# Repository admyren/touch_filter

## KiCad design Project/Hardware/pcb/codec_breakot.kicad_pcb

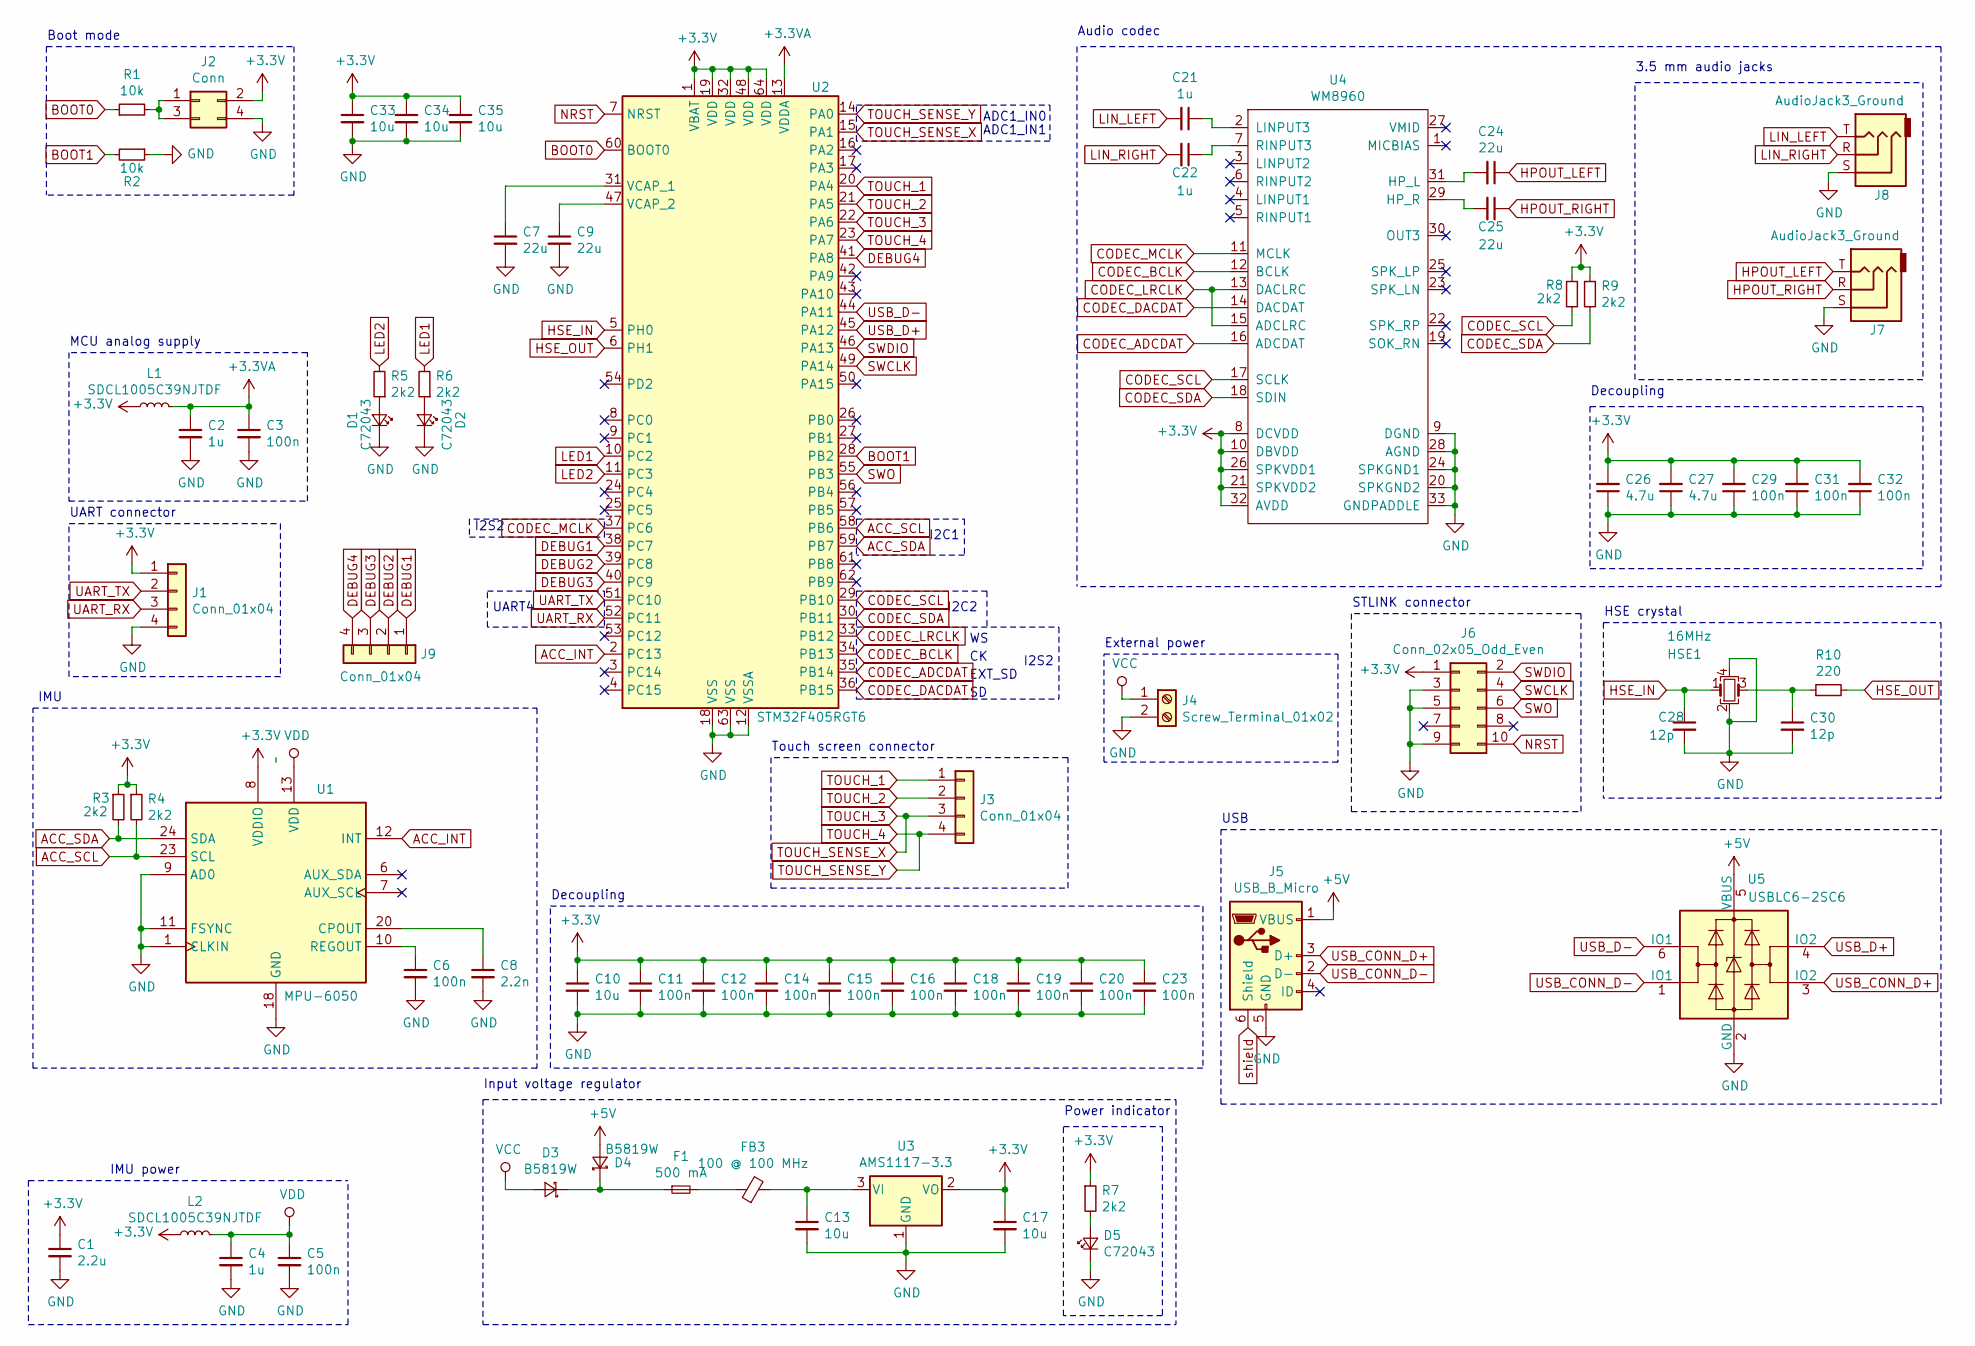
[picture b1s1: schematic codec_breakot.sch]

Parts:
C1: 2.2u; C_0603; LCSC Part # C23630
C2, C4, C21, C22: 1u; C_0603; LCSC Part # C15849
C3, C5, C6, C11, C12, C14, C15, C16, C18, C19, C20, C23, C29, C31, C32: 100n; C_0603; LCSC Part # C14663
C7, C9, C24, C25: 22u; C_0805; LCSC Part # C45783
C8: 2.2n; C_0402; LCSC Part # C1531
C10, C13, C17, C33, C34, C35: 10u; C_0805; LCSC Part # C15850
C26, C27: 4.7u; C_0603; LCSC Part # C19666
C28, C30: 12p; C_0402; LCSC Part # C1547
D1, D2, D5: C72043; LED_0603; LCSC Part # C72043
D3, D4: B5819W; D_SOD-123; LCSC Part # C8598
F1: 500 mA; Fuse_SMD1206_HandSoldering
FB3: 100 @ 100 MHz; L_0805_2012Metric
HSE1: 16MHz; Crystal_SMD_3225-4pin_3.2x2.5mm; LCSC Part # C13738
J1: Conn_01x04; Pin_Header_Straight_1x04_Pitch2.54mm
J2: Conn; Pin_Header_Straight_2x02_Pitch2.54mm
J3: Conn_01x04; conn_pad_SMD_1x4_1mm
J4: Screw_Terminal_01x02; Pin_Header_Straight_1x02_Pitch2.54mm
J5: USB_B_Micro; USB_micro_smd
J6: Conn_02x05_Odd_Even; Pin_Header_Straight_2x05_Pitch2.54mm
J7, J8: AudioJack3_Ground; Jack_3.5mm_CUI_SJ-3523-SMT_Horizontal
J9: Conn_01x04; Pin_Header_Straight_1x04_Pitch1.27mm
L1, L2: SDCL1005C39NJTDF; L_0402_1005Metric; LCSC Part # C26443
R1, R2: 10k; R_0402; LCSC Part # C25744
R3, R4, R5, R6, R7, R8, R9: 2k2; R_0402; LCSC Part # C25879
R10: 220; R_0603; LCSC Part # C22962
U1: MPU-6050; QFN-24_4x4_Pitch0.5mm; LCSC Part # C24112
U2: STM32F405RGT6; LQFP-64_10x10mm_Pitch0.5mm; LCSC Part # C15742
U3: AMS1117-3.3; SOT-223-3_TabPin2; LCSC Part # C6186
U4: WM8960; QFN-32-1EP_5x5mm_Pitch0.5mm; LCSC Part # C18752
U5: USBLC6-2SC6; SOT-23-6; LCSC Part # C7519

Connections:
+3.3VA: C2.1, C3.1, L1.2, U2.13 (VDDA)
+3V3: C1.1, C10.1, C11.1, C12.1, C14.1, C15.1, C16.1, C17.1, C18.1, C19.1, C20.1, C23.1, C26.2, C27.2, C29.2, C31.2, C32.2, C33.1, C34.1, C35.1, J1.1, J2.2, J6.1, L1.1, L2.1, R3.1, R4.1, R7.1, R8.1, R9.1, U1.8 (VDDIO), U2.1 (VBAT), U2.19 (VDD), U2.32 (VDD), U2.48 (VDD), U2.64 (VDD), U3.2 (VO), U4.8 (DCVDD), U4.10 (DBVDD), U4.21 (SPKVDD2), U4.26 (SPKVDD1), U4.32 (AVDD)
+5V: D4.2 (A), J5.1 (VBUS), U5.5 (VBUS)
ACC_INT: U1.12 (INT), U2.2 (PC13)
ACC_SCL: R4.2, U1.23 (SCL), U2.58 (PB6)
ACC_SDA: R3.2, U1.24 (SDA), U2.59 (PB7)
BOOT0: R1.1, U2.60 (BOOT0)
BOOT1: R2.2, U2.28 (PB2)
CODEC_ADCDAT: U2.35 (PB14), U4.16 (ADCDAT)
CODEC_BCLK: U2.34 (PB13), U4.12 (BCLK)
CODEC_DACDAT: U2.36 (PB15), U4.14 (DACDAT)
CODEC_LRCLK: U2.33 (PB12), U4.13 (DACLRC), U4.15 (ADCLRC)
CODEC_MCLK: U2.37 (PC6), U4.11 (MCLK)
CODEC_SCL: R8.2, U2.29 (PB10), U4.17 (SCLK)
CODEC_SDA: R9.2, U2.30 (PB11), U4.18 (SDIN)
DEBUG1: J9.1, U2.38 (PC7)
DEBUG2: J9.2, U2.39 (PC8)
DEBUG3: J9.3, U2.40 (PC9)
DEBUG4: J9.4, U2.41 (PA8)
GND: C1.2, C2.2, C3.2, C4.2, C5.2, C6.2, C7.2, C8.2, C9.2, C10.2, C11.2, C12.2, C13.2, C14.2, C15.2, C16.2, C17.2, C18.2, C19.2, C20.2, C23.2, C26.1, C27.1, C28.2, C29.1, C30.2, C31.1, C32.1, C33.2, C34.2, C35.2, D1.1 (K), D2.1 (K), D5.1 (K), HSE1.2, HSE1.4, J1.4, J2.4, J4.2, J5.5 (GND), J6.3, J6.5, J6.9, J7.S, J8.S, R2.1, U1.1 (CLKIN), U1.9 (AD0), U1.11 (FSYNC), U1.18 (GND), U2.12 (VSSA), U2.18 (VSS), U2.63 (VSS), U3.1 (GND), U4.9 (DGND), U4.20 (SPKGND2), U4.24 (SPKGND1), U4.28 (AGND), U4.33 (GNDPADDLE), U5.2 (GND)
HPOUT_LEFT: C24.1, J7.T
HPOUT_RIGHT: C25.1, J7.R
HSE_IN: C28.1, HSE1.1, U2.5 (PH0)
HSE_OUT: R10.2, U2.6 (PH1)
LED1: R6.2, U2.10 (PC2)
LED2: R5.2, U2.11 (PC3)
LIN_LEFT: C21.2, J8.T
LIN_RIGHT: C22.2, J8.R
NRST: J6.10, U2.7 (NRST)
unnamed: C6.1, U1.10 (REGOUT)
unnamed: C7.1, U2.31 (VCAP_1)
unnamed: C8.1, U1.20 (CPOUT)
unnamed: C9.1, U2.47 (VCAP_2)
unnamed: C13.1, FB3.2, U3.3 (VI)
unnamed: C21.1, U4.2 (LINPUT3)
unnamed: C22.1, U4.7 (RINPUT3)
unnamed: C24.2, U4.31 (HP_L)
unnamed: C25.2, U4.29 (HP_R)
unnamed: C30.1, HSE1.3, R10.1
unnamed: D1.2 (A), R5.1
unnamed: D2.2 (A), R6.1
unnamed: D3.1 (K), D4.1 (K), F1.1
unnamed: D5.2 (A), R7.2
unnamed: F1.2, FB3.1
unnamed: J2.1, J2.3, R1.2
SWCLK: J6.4, U2.49 (PA14)
SWDIO: J6.2, U2.46 (PA13)
SWO: J6.6, U2.55 (PB3)
TOUCH_1: J3.1, U2.20 (PA4)
TOUCH_2: J3.2, U2.21 (PA5)
TOUCH_3: J3.3, U2.15 (PA1), U2.22 (PA6)
TOUCH_4: J3.4, U2.14 (PA0), U2.23 (PA7)
UART_RX: J1.3, U2.52 (PC11)
UART_TX: J1.2, U2.51 (PC10)
USB_CONN_D+: J5.3 (D+), U5.3 (IO2)
USB_CONN_D-: J5.2 (D-), U5.1 (IO1)
USB_D+: U2.45 (PA12), U5.4 (IO2)
USB_D-: U2.44 (PA11), U5.6 (IO1)
VCC: D3.2 (A), J4.1
VDD: C4.1, C5.1, L2.2, U1.13 (VDD)
shield: J5.6 (Shield)

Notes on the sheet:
Input voltage regulator
Power indicator
Decoupling
3.5 mm audio jacks
Audio codec
USB
STLINK connector
HSE crystal
Boot mode
MCU analog supply
IMU power
I2C2
I2S2
I2C1
UART4
ADC1_IN0
ADC1_IN1
IMU
Touch screen connector
UART connector
External power
EXT_SD

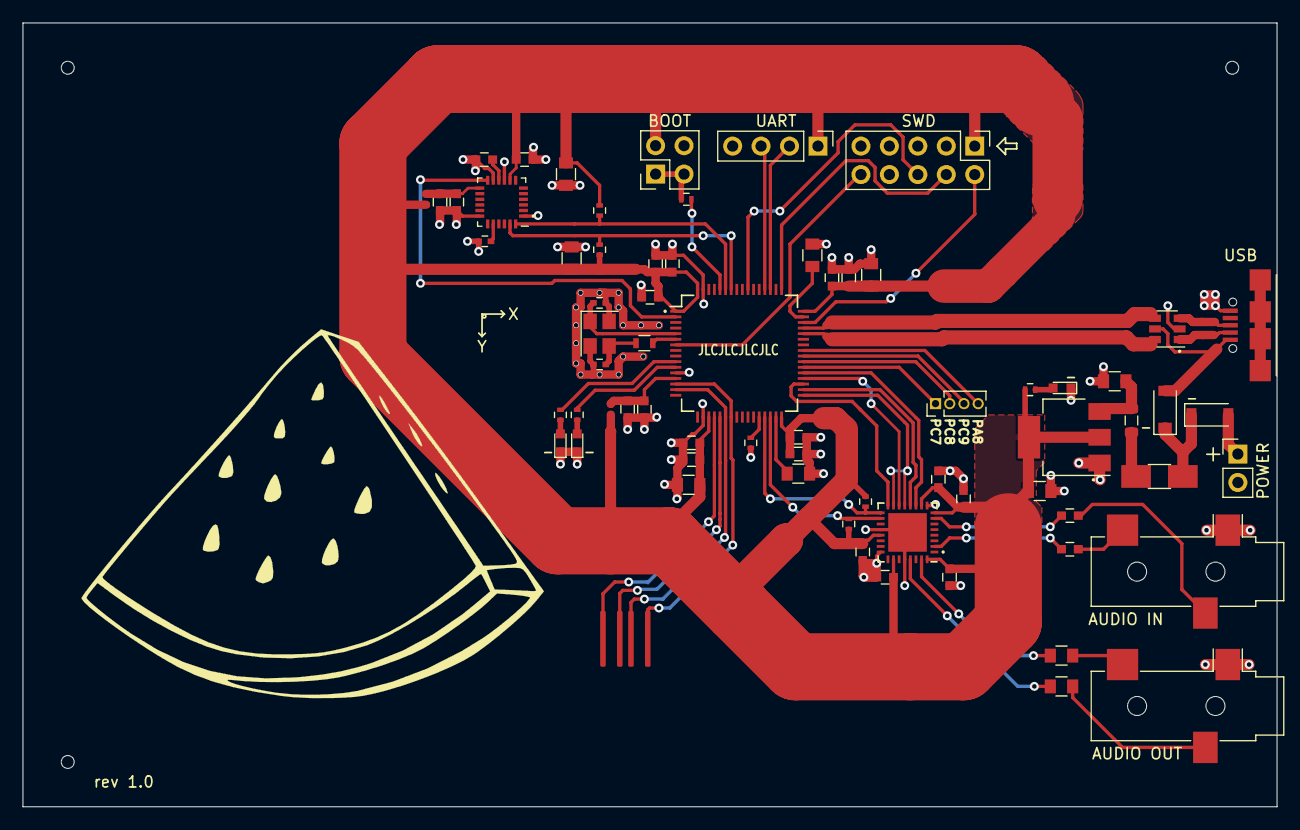
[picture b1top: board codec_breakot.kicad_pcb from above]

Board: 2 copper layers, 112.0 x 70.0 mm, 72 parts (0 on the bottom side), 60 nets.

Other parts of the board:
TOOLING HOLE: jlcpcb_tooling_hole
TOOLING HOLE#2, TOOLING HOLE#3: jlcpcb_tooling_hole

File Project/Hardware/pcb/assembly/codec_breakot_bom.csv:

Comment,Designator,Footprint,LCSC
"2.2u","C1","Capacitors_SMD:C_0603","C23630"
"10u","C10,C13,C17,C33,C34,C35","Capacitors_SMD:C_0805","C15850"
"1u","C2,C4,C21,C22","Capacitors_SMD:C_0603","C15849"
"22u","C7,C9,C24,C25","Capacitors_SMD:C_0805","C45783"
"4.7u","C26,C27","Capacitors_SMD:C_0603","C19666"
"12p","C28,C30","Capacitors_SMD:C_0402","C1547"
"100n","C3,C5,C6,C11,C12,C14,C15,C16,C18,C19,C20,C23,C29,C31,C32","Capacitors_SMD:C_0603","C14663"
"2.2n","C8","Capacitors_SMD:C_0402","C1531"
"B5819W","D3,D4","Diodes_SMD:D_SOD-123","C8598"
"C72043","D1,D2,D5","LEDs:LED_0603","C72043"
"500 mA","F1","Fuse_Holders_and_Fuses:Fuse_SMD1206_HandSoldering",""
"100 @ 100 MHz","FB3","Inductor_SMD:L_0805_2012Metric",""
"16MHz","HSE1","Crystals:Crystal_SMD_3225-4pin_3.2x2.5mm","C13738"
"Conn_01x04","J1","Pin_Headers:Pin_Header_Straight_1x04_Pitch2.54mm",""
"Conn","J2","Pin_Headers:Pin_Header_Straight_2x02_Pitch2.54mm",""
"Conn_01x04","J3","egna_footprints:conn_pad_SMD_1x4_1mm",""
"Screw_Terminal_01x02","J4","Pin_Headers:Pin_Header_Straight_1x02_Pitch2.54mm",""
"USB_B_Micro","J5","egna_footprints:USB_micro_smd",""
"Conn_02x05_Odd_Even","J6","Pin_Headers:Pin_Header_Straight_2x05_Pitch2.54mm",""
"AudioJack3_Ground","J7,J8","Connector_Audio:Jack_3.5mm_CUI_SJ-3523-SMT_Horizontal",""
"Conn_01x04","J9","Pin_Headers:Pin_Header_Straight_1x04_Pitch1.27mm",""
"SDCL1005C39NJTDF","L1,L2","Inductor_SMD:L_0402_1005Metric","C26443"
"10k","R1,R2","Resistors_SMD:R_0402","C25744"
"220","R10","Resistors_SMD:R_0603","C22962"
"2k2","R3,R4,R5,R6,R7,R8,R9","Resistors_SMD:R_0402","C25879"
"MPU-6050","U1","egna_footprints:QFN-24_4x4_Pitch0.5mm","C24112"
"STM32F405RGT6","U2","Housings_QFP:LQFP-64_10x10mm_Pitch0.5mm","C15742"
"AMS1117-3.3","U3","TO_SOT_Packages_SMD:SOT-223-3_TabPin2","C6186"
"WM8960","U4","Housings_DFN_QFN:QFN-32-1EP_5x5mm_Pitch0.5mm","C18752"
"USBLC6-2SC6","U5","TO_SOT_Packages_SMD:SOT-23-6","C7519"

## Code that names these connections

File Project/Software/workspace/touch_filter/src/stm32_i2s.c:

/*
 * stm32_i2s.c
 *
 *  Created on: 11 sep. 2021
 *      Author: Myren
 */
#include <stdint.h>

#include "stm32f405xx.h"
#include "stm32_i2s.h"
#include "stm32_dma.h"

void (*I2S_tx_ready_callb)(void) = 0;
void (*I2S_rx_ready_callb)(void) = 0;


void i2s_config(uint16_t* rx_buff, uint16_t* tx_buff, uint32_t buff_size)
{
   /* Struct for configuring DMA */
   DMA_InitVals DMA_init;

   /* I2S2ext, I2S2 (SPI2) */

   /* Enable I2S2 (SPI2) peripheral clock */
   RCC->APB1ENR |= (1 << 14);

   /* Configure GPIO used by I2S */
   /*
   MCLK - PC6
   LRCLK (WS) - PB12
   BCLK (CK) - PB13
   ADCDAT (EXT_SD) - PB14
   DACDAT (SD) - PB15
   */

   /* Enable GPIOB peripheral clock */
   RCC->AHB1ENR |= (1 << 1);
   /* Enable GPIOC peripheral clock */
   RCC->AHB1ENR |= (1 << 2);
   /* Alternate function */
   GPIOB->MODER |= (2 << 30) | (2 << 28) | (2 << 26) | (2 << 24);
   GPIOC->MODER |= (2 << 12);
   /* I2S2ext is on AF6, I2S2 is on AF5 */
   GPIOB->AFR[1] |= (5 << 28) | (6 << 24) | (5 << 20) | (5 << 16);
   GPIOC->AFR[0] |= (5 << 24);

   /* Set ODD bit and I2SDIV value */
   SPI2->I2SPR |= (1 << 8) | 3u;

   /* Select clock polarity */
   SPI2->I2SCFGR &= ~(1 << 3);

   /* Enable master output clock to audio CODEC */
   SPI2->I2SPR |= (1 << 9);

   /* Select mode: I2S */
   SPI2->I2SCFGR |= (1 << 11);

   /* Chose I2S standard */
   SPI2->I2SCFGR &= ~(3u << 4);

   /* Select data length, 16-bit */
   SPI2->I2SCFGR &= ~(3u << 1);

   /* Select nr of bits per channel, 16-bit */
   SPI2->I2SCFGR &= ~(0x1);

   /* Select I2S master transmit mode */
   SPI2->I2SCFGR |= (2u << 8);

   /***** Enable I2S2ext in slave receiver mode to achieve full duplex com *****/
   /* Select mode: I2S */
   I2S2ext->I2SCFGR |= (1 << 11);
   /* Chose I2S standard */
   I2S2ext->I2SCFGR &= ~(3u << 4);
   /* Select data length, 16-bit */
   I2S2ext->I2SCFGR &= ~(3u << 1);
   /* Select nr of bits per channel, 16-bit */
   I2S2ext->I2SCFGR &= ~(0x1);
   /* Select I2S slave receiver mode */
   I2S2ext->I2SCFGR |= (1u << 8);

#if 1
   /* Configure DMA */
   /* DMA clocks */
   RCC->AHB1ENR |= (1 << 22) | (1 << 21);
   /* I2S2 TX uses stream 4, ch 0. I2Sext RX uses stream 2, ch 2  */
   /* Enable TX DMA  */
   SPI2->CR2 |= (1 << 1);
   /* Enable RX DMA */
   I2S2ext->CR2 |= (1 << 0);


   DMA_init.channel = 0;             /* DMA channel */
   DMA_init.periphDataSize = SIZE_HALF_WORD;      /* Peripheral data size */
   DMA_init.memDataSize = SIZE_HALF_WORD;         /* Memory data size */
   DMA_init.direction = 1;           /* Direction, memory->peripheral(1) or peripheral->memory(0) */
   DMA_init.bufferSize = buff_size;          /* Number of element in the DMA buffer */
   DMA_init.periphAddr = (uint32_t)(&SPI2->DR);          /* Address to peripheral data register */
   DMA_init.memAddr = (uint32_t)tx_buff;             /* Address to first element of DMA buffer */
   DMA_init.halfIntEnable = 0;       /* DMA half transfer complete interrupt enable */
   DMA_init.compIntEnable = 1;       /* DMA transfer complete interrupt enable */
   DMA_init.mode = 1;                /* Circular mode or not */
   DMA_init.dma_enable = 1;          /* DMA enable */

   /* Enable DMA for I2S2 TX */
   DMA_config(DMA1_Stream4, DMA_init);

   DMA_init.channel = 2;             /* DMA channel */
   DMA_init.periphDataSize = SIZE_HALF_WORD;      /* Peripheral data size */
   DMA_init.memDataSize = SIZE_HALF_WORD;         /* Memory data size */
   DMA_init.direction = 0;           /* Direction, memory->peripheral(1) or peripheral->memory(0) */
   DMA_init.bufferSize = buff_size;          /* Number of element in the DMA buffer */
   DMA_init.periphAddr = (uint32_t)(&I2S2ext->DR);          /* Address to peripheral data register */
   DMA_init.memAddr = (uint32_t)rx_buff;             /* Address to first element of DMA buffer */
   DMA_init.halfIntEnable = 0;       /* DMA half transfer complete interrupt enable */
   DMA_init.compIntEnable = 1;       /* DMA transfer complete interrupt enable */
   DMA_init.mode = 1;                /* Circular mode or not */
   DMA_init.dma_enable = 1;          /* DMA enable */

   /* Enable DMA for I2S2ext RX */
   DMA_config(DMA1_Stream2, DMA_init);

   NVIC_SetPriorityGrouping(2);
   NVIC_SetPriority (DMA1_Stream2_IRQn, 8);
   NVIC_EnableIRQ(DMA1_Stream2_IRQn);

   NVIC_SetPriorityGrouping(2);
   NVIC_SetPriority (DMA1_Stream4_IRQn, 8);
   NVIC_EnableIRQ(DMA1_Stream4_IRQn);
#endif

   /* Enable I2S */
   SPI2->I2SCFGR |= (1 << 10);
   I2S2ext->I2SCFGR |= (1 << 10);

}

void I2S_register_rx_complete_callback(void (*func)(void))
{
   I2S_rx_ready_callb = func;
}

void I2S_register_tx_complete_callback(void (*func)(void))
{
   I2S_tx_ready_callb = func;
}


void DMA1_Stream2_IRQHandler(void)
{
   // Transfer complete interrupt?
   if(DMA1->LISR & (1 << 21))
   {
      // Clear interrupt flag
      DMA1->LIFCR |= 1 << 21;

      if (I2S_rx_ready_callb != 0)
      {
         I2S_rx_ready_callb();
      }
   }
}

void DMA1_Stream4_IRQHandler(void)
{
   // Transfer complete interrupt?
   if(DMA1->HISR & (1 << 5))
   {
      // Clear interrupt flag
      DMA1->HIFCR |= 1 << 5;

      if(I2S_tx_ready_callb != 0)
      {
         I2S_tx_ready_callb();
      }
   }
}

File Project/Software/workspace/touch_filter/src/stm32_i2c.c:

/*
 * stm32_i2c.c
 *
 *  Created on: 28 aug. 2021
 *      Author: Myren
 */

/*
 * i2c_drv.c
 *
 *  Created on: 11 jan. 2020
 *      Author: Myren
 */

#include "stm32f405xx.h"
#include "stm32_i2c.h"
#include "stm32_gpio.h"
#include "stm32_peripherals.h"

/*
 Codec uses I2C2, SCL: PB10 SDA: PB11
 IMU uses I2C1, SCL: PB6 SDA: PB7
*/

void i2c1_init(I2C_TypeDef* hi2c)
{
   // This initializes the I2C1 peripheral
   // and its corresponding GPIOs

   uint32_t pclk1;
   const uint32_t scl_freq = 100000;
   gpio_config_t gpio_conf;


   gpio_conf.mode = gpio_af;
   gpio_conf.output_type = gpio_ood;
   gpio_conf.output_speed = gpio_hs;
   gpio_conf.pull_up_down = gpio_no_pull;
   gpio_conf.alternate_func = gpio_af_4;
   gpio_conf.lock = gpio_lock_off;
   gpio_conf.pins = gpio_pin_10 | gpio_pin_11;

   // Enable GPIOB peripheral clock
   RCC->AHB1ENR |= (1 << 1);

   //gpio_init(GPIOB, &gpio_conf);

#if 1
   // Alternate function
   GPIOB->MODER |= (2 << 14) | (2 << 12);
   // AF4 alternate function
   GPIOB->AFR[0] |= (4 << 28) | (4 << 24);
#endif

   // Enable I2C1 peripheral clock
   RCC->APB1ENR |= (1 << 21);

   // Periperal clock freqiency in MHz, 50MHz >= FREQ >= 2MHz
   hi2c->CR2 |= (0x001f & 42u);

   // Set fast mode (400khz)
   //I2C1->CCR |= (1 << 15);

   // Set fast mode duty
   // I2C1->CCR |= (1 << 14);
   // Get frequency of peripheral clock
   //pclk1 = HAL_RCC_GetPCLK1Freq();
   pclk1 = 42000000;
   // Clock control, for an SCL freq. of approx. 100 kHz
   //hi2c->CCR |= 0x0fff & (2*pclk1/scl_freq);
   /* 100 kHz */
   hi2c->CCR |= 210;

   // Maximum rise time of SCL, programmed with
   // rise =(max_rise_t/T_PCLK1)+1. Where T_PCLK1 is the
   // period time of the peripheral clock and max_rise_t
   // is the maximum rise time of SCL specified by the I2C specification.

   //hi2c->TRISE |= (0x003f & ((pclk1/1000) + 1));
   hi2c->TRISE |= (0x003f & ((pclk1/1000000) + 1));

   // Peripheral enable
   hi2c->CR1 |= (1 << 0);
}

void i2c2_init(I2C_TypeDef* hi2c)
{
   // This initializes the I2C2 peripheral
   // and its corresponding GPIOs

   uint32_t pclk1;
   const uint32_t scl_freq = 100000;
   gpio_config_t gpio_conf;


   gpio_conf.mode = gpio_af;
   gpio_conf.output_type = gpio_ood;
   gpio_conf.output_speed = gpio_hs;
   gpio_conf.pull_up_down = gpio_no_pull;
   gpio_conf.alternate_func = gpio_af_4;
   gpio_conf.lock = gpio_lock_off;
   gpio_conf.pins = gpio_pin_10 | gpio_pin_11;

   // Enable GPIOB peripheral clock
   RCC->AHB1ENR |= (1 << 1);

   //gpio_init(GPIOB, &gpio_conf);

#if 1
   // Alternate function
   GPIOB->MODER |= (2 << 22) | (2 << 20);
   // AF4 alternate function
   GPIOB->AFR[1] |= (4 << 12) | (4 << 8);
#endif

   // Enable I2C2 peripheral clock
   RCC->APB1ENR |= (1 << 22);

   // Periperal clock freqiency in MHz, 50MHz >= FREQ >= 2MHz
   hi2c->CR2 |= (0x001f & 42u);

   // Set fast mode (400khz)
   //I2C1->CCR |= (1 << 15);

   // Set fast mode duty
   // I2C1->CCR |= (1 << 14);
   // Get frequency of peripheral clock
   //pclk1 = HAL_RCC_GetPCLK1Freq();
   pclk1 = 42000000;
   // Clock control, for an SCL freq. of approx. 100 kHz
   /* 100 kHz */
   hi2c->CCR |= 210;

   // Maximum rise time of SCL, programmed with
   // rise =(max_rise_t/T_PCLK1)+1. Where T_PCLK1 is the
   // period time of the peripheral clock and max_rise_t
   // is the maximum rise time of SCL specified by the I2C specification.

   hi2c->TRISE |= (0x003f & ((pclk1/1000000) + 1));

   // Peripheral enable
   hi2c->CR1 |= (1 << 0);
}

uint32_t i2c_start(I2C_TypeDef* hi2c)
{
   uint32_t ret = 0;
   uint32_t timeout_cnt = 0;
   // Start generation
   hi2c->CR1 |= (1 << 8);
   //Check if a start condition has been generated
   while(!(hi2c->SR1 & (1 << 0)))
   {
      timeout_cnt++;
      if (timeout_cnt > TIMEOUT_WAIT_COUNT)
      {
         ret = 1;
         break;
      }
   }
   return ret;
}

void i2c_stop(I2C_TypeDef* hi2c)
{
   // Stop generation
   hi2c->CR1 |= (1 << 9);
}

uint32_t i2c_checkReady(I2C_TypeDef* hi2c)
{
   uint32_t ret = 0;
   uint32_t timeout_cnt = 0;
   // Check so the bus is not busy
   while(hi2c->SR2 & (1 << 1))
   {
      timeout_cnt++;
      if(timeout_cnt > TIMEOUT_WAIT_COUNT)
      {
         ret = 1;
         break;
      }
   }

   return ret;
}

uint32_t i2c_sendAddress(I2C_TypeDef* hi2c, uint8_t addr)
{
   uint32_t ret = 0;
   uint32_t timeout_cnt = 0;

   hi2c->DR = addr;


   // Wait until the ADDR bit is set
   while(!(hi2c->SR1 & (1 << 1)))
   {
      timeout_cnt++;
      if(timeout_cnt > TIMEOUT_WAIT_COUNT)
      {
         ret = 1;
         break;
      }
   }

   volatile uint32_t dummy = I2C1->SR2;
   (void)dummy;

   return ret;
}

uint32_t i2c_sendData(I2C_TypeDef* hi2c, uint8_t data)
{
   uint32_t ret = 0;
   uint32_t timeout_cnt = 0;

   hi2c->DR = data;
   while(!(hi2c->SR1 & (1 << 7)))
   {
      timeout_cnt++;
      if(timeout_cnt > TIMEOUT_WAIT_COUNT)
      {
         ret = 1;
         break;
      }
   }

   return ret;
}

uint32_t i2c_check_ack(I2C_TypeDef* hi2c)
{
   uint32_t ret = 0;

   if (hi2c->SR1 & (1 << 10))
   {
      ret = 1; // Failure
   }

   return ret;
}

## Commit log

2021-09-18 Implement UART
2021-09-21 Add .gitignore
2021-09-21 Start ignoring .metadata/
2021-09-21 Start ignoring generated files
2021-09-21 Updated .gitignore
2021-10-18 Haft the i2s DMA up and running
